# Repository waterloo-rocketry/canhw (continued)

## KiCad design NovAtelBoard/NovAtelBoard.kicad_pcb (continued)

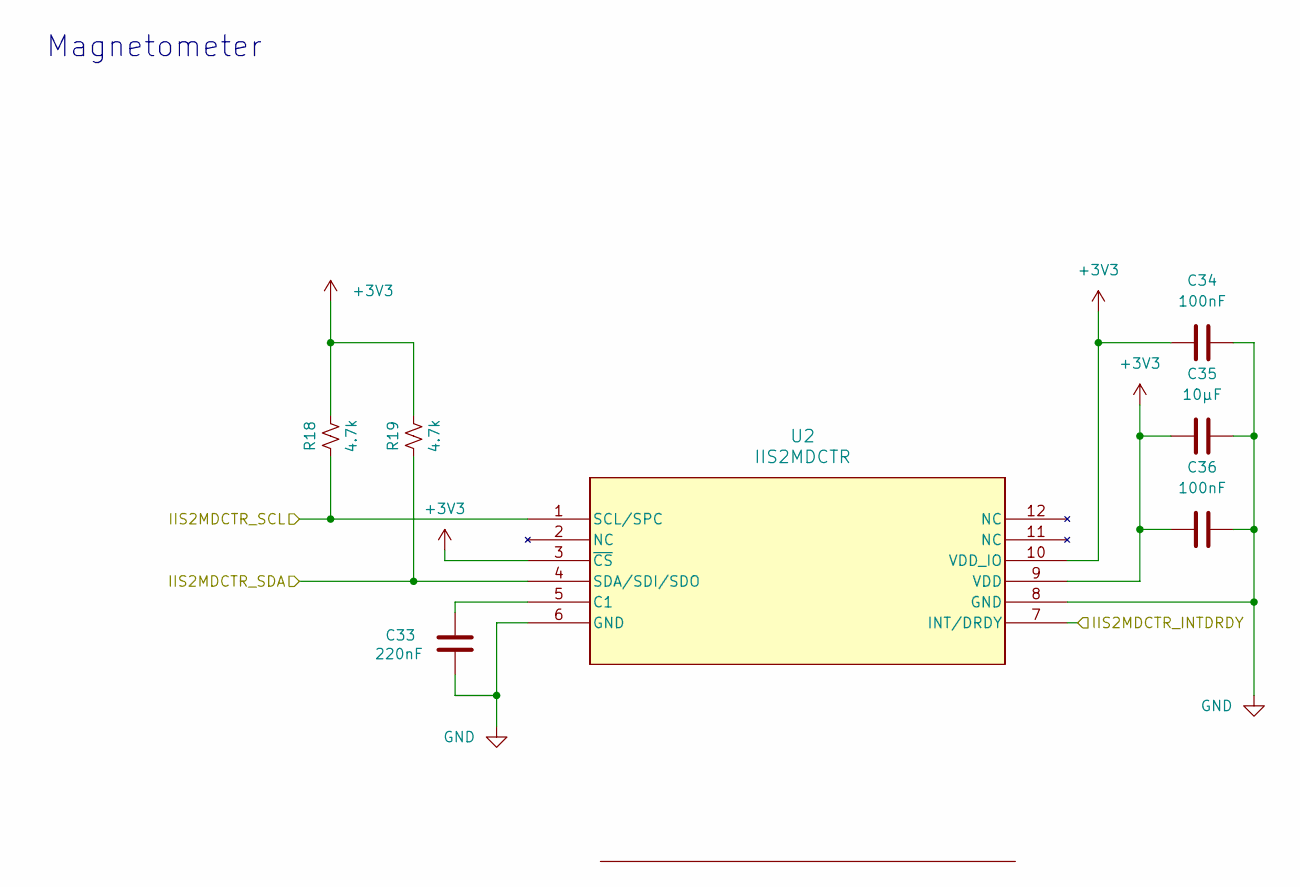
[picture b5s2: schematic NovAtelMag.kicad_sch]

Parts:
C33: 220nF; C_0603_1608Metric_Pad1.08x0.95mm_HandSolder
C34, C36: 100nF; C_0603_1608Metric_Pad1.08x0.95mm_HandSolder
C35: 10μF; C_0603_1608Metric_Pad1.08x0.95mm_HandSolder
R18, R19: 4.7k; R_0402_1005Metric; LCSC Part # C144773
U2: IIS2MDCTR; LGA-12_2X2X0P7_STM

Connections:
+3V3: C34.1, C35.2, C36.2, R18.1, R19.1, U2.3 (~CS), U2.9 (VDD), U2.10 (VDD_IO); also elsewhere on the board
/NovAtelMag/IIS2MDCTR_INTDRDY: U2.7 (INT/DRDY); also elsewhere on the board
/NovAtelMag/IIS2MDCTR_SCL: R18.2, U2.1 (SCL/SPC); also elsewhere on the board
/NovAtelMag/IIS2MDCTR_SDA: R19.2, U2.4 (SDA/SDI/SDO); also elsewhere on the board
GND: C33.1, C34.2, C35.1, C36.1, U2.6 (GND), U2.8 (GND); also elsewhere on the board
unnamed: C33.2, U2.5 (C1)

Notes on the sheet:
Magnetometer

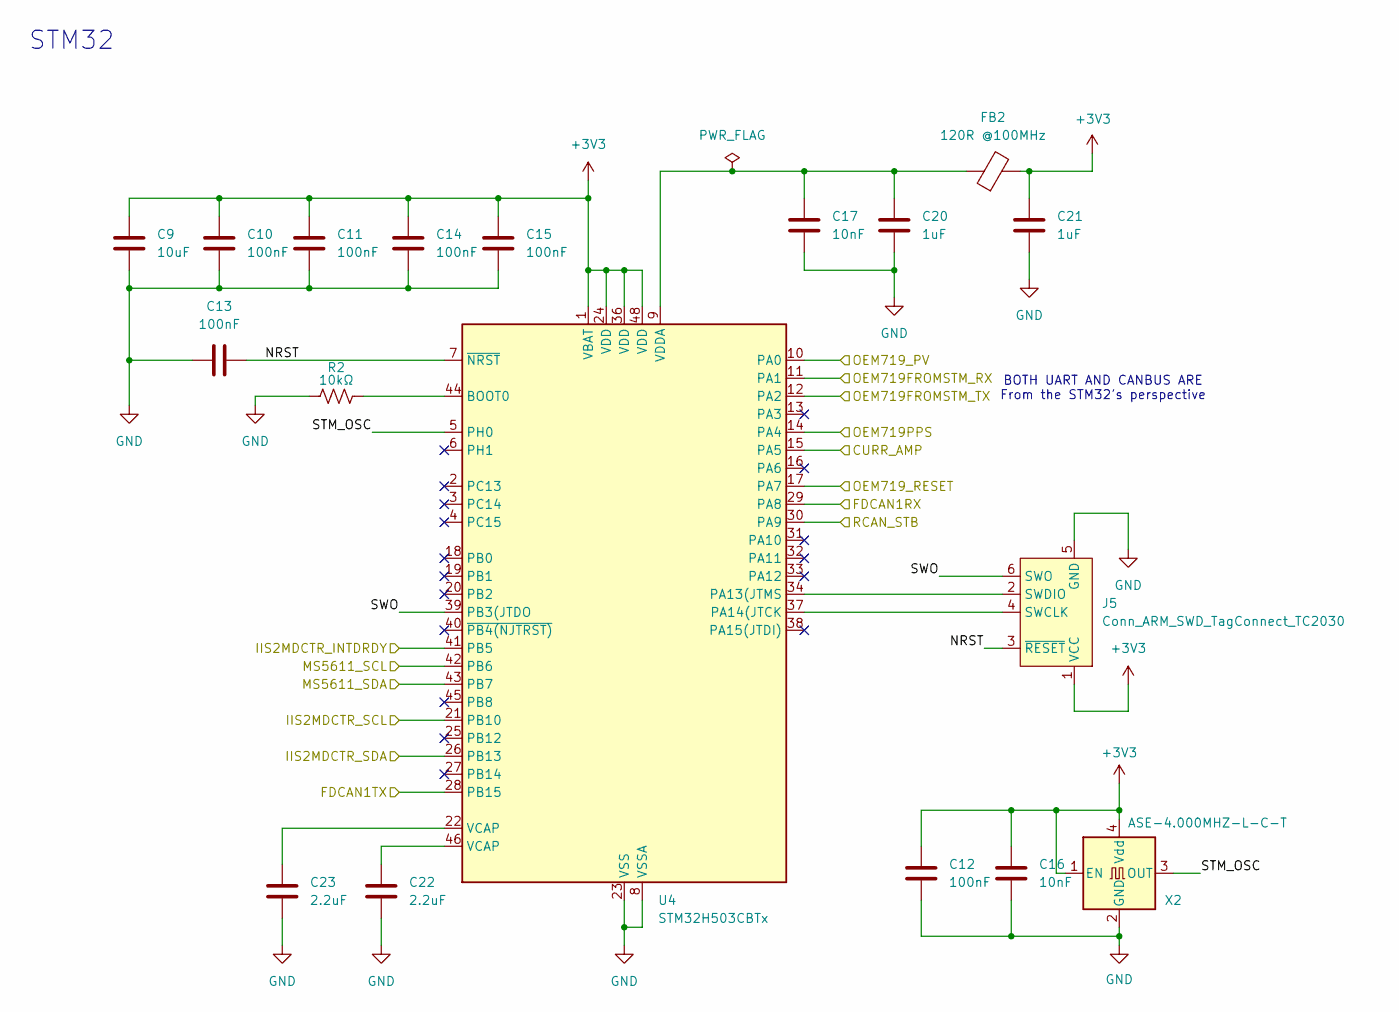
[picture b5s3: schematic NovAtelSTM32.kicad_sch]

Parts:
C9: 10uF; C_0603_1608Metric_Pad1.08x0.95mm_HandSolder
C10, C11, C12, C13, C14, C15: 100nF; C_0603_1608Metric_Pad1.08x0.95mm_HandSolder
C16, C17: 10nF; C_0603_1608Metric_Pad1.08x0.95mm_HandSolder
C20, C21: 1uF; C_0603_1608Metric_Pad1.08x0.95mm_HandSolder
C22, C23: 2.2uF; C_0603_1608Metric_Pad1.08x0.95mm_HandSolder
FB2: 120R @100MHz
J5: Conn_ARM_SWD_TagConnect_TC2030; Tag-Connect_TC2030-IDC-FP_2x03_P1.27mm_Vertical
R2: 10kΩ; R_Array_SIP4
U4: STM32H503CBTx; LQFP-48_7x7mm_P0.5mm
X2: ASE-4.000MHZ-L-C-T; Oscillator_SMD_Abracon_ASE-4Pin_3.2x2.5mm; LCSC Part # C437121

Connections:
+3V3: C9.1, C10.1, C11.1, C12.1, C14.1, C15.1, C16.1, C21.1, FB2.2, J5.1 (VCC), U4.1 (VBAT), U4.24 (VDD), U4.36 (VDD), U4.48 (VDD), X2.1 (EN), X2.4 (Vdd); also elsewhere on the board
/NovAtelBaro/MS5611_SCL: U4.42 (PB6); also elsewhere on the board
/NovAtelBaro/MS5611_SDA: U4.43 (PB7); also elsewhere on the board
/NovAtelConnAndCan/CURR_AMP: U4.15 (PA5); also elsewhere on the board
/NovAtelConnAndCan/FDCAN1RX: U4.29 (PA8); also elsewhere on the board
/NovAtelConnAndCan/FDCAN1TX: U4.28 (PB15); also elsewhere on the board
/NovAtelConnAndCan/RCAN_STB: U4.30 (PA9); also elsewhere on the board
/NovAtelHeader/OEM719PPS: U4.14 (PA4); also elsewhere on the board
/NovAtelHeader/OEM719_PV: U4.10 (PA0); also elsewhere on the board
/NovAtelHeader/OEM719_RX: U4.12 (PA2); also elsewhere on the board
/NovAtelHeader/OEM719_TX: U4.11 (PA1); also elsewhere on the board
/NovAtelHeader/~OEM719_RESET: U4.17 (PA7); also elsewhere on the board
/NovAtelMag/IIS2MDCTR_INTDRDY: U4.41 (PB5); also elsewhere on the board
/NovAtelMag/IIS2MDCTR_SCL: U4.21 (PB10); also elsewhere on the board
/NovAtelMag/IIS2MDCTR_SDA: U4.26 (PB13); also elsewhere on the board
/NovAtelSTM32/NRST: C13.1, J5.3 (~RESET), U4.7 (~NRST)
/NovAtelSTM32/STM_OSC: U4.5 (PH0), X2.3 (OUT)
/NovAtelSTM32/SWO: J5.6 (SWO), U4.39 (PB3(JTDO)
GND: C9.2, C10.2, C11.2, C12.2, C13.2, C14.2, C15.2, C16.2, C17.2, C20.2, C21.2, C22.2, C23.2, J5.5 (GND), R2.1, U4.8 (VSSA), U4.23 (VSS), U4.35 (VSS), U4.47 (VSS), X2.2 (GND); also elsewhere on the board
unnamed: C22.1, U4.46 (VCAP)
unnamed: C23.1, U4.22 (VCAP)
unnamed: J5.4 (SWCLK), U4.37 (PA14(JTCK)
unnamed: J5.2 (SWDIO), U4.34 (PA13(JTMS)
unnamed: R2.2, U4.44 (BOOT0)
unnamed: C17.1, C20.1, FB2.1, U4.9 (VDDA)

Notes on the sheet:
STM32
BOTH UART AND CANBUS ARE From the STM32's perspective

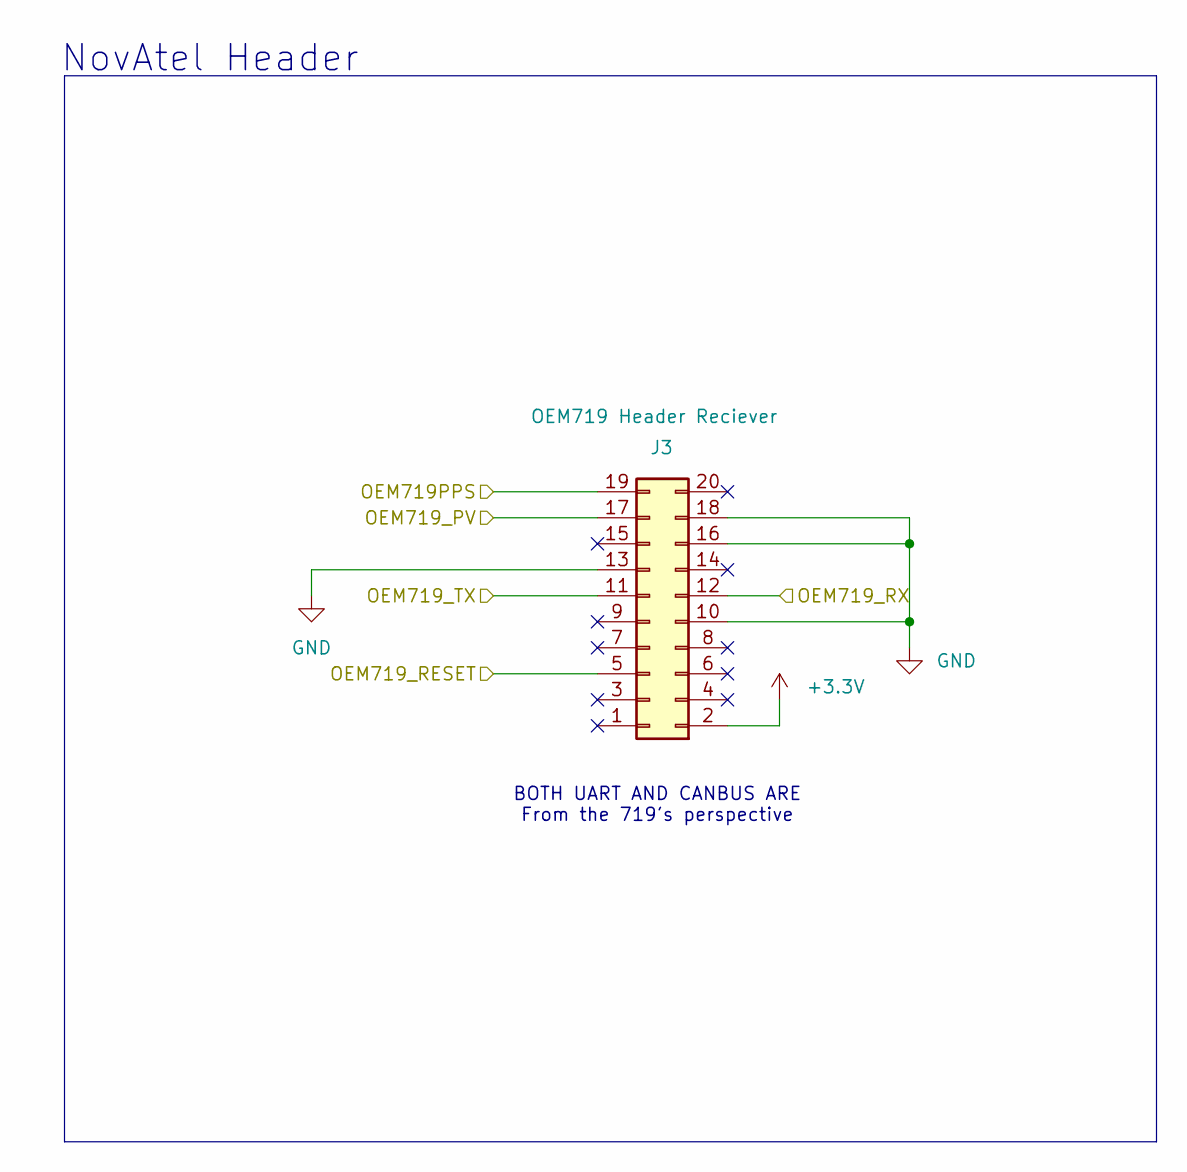
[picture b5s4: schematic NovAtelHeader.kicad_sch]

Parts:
J3: OEM719 Header Reciever

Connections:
unnamed: J3.10 (GND), J3.13 (GND), J3.16 (GND), J3.18 (GND)

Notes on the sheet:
NovAtel Header
BOTH UART AND CANBUS ARE From the 719's perspective

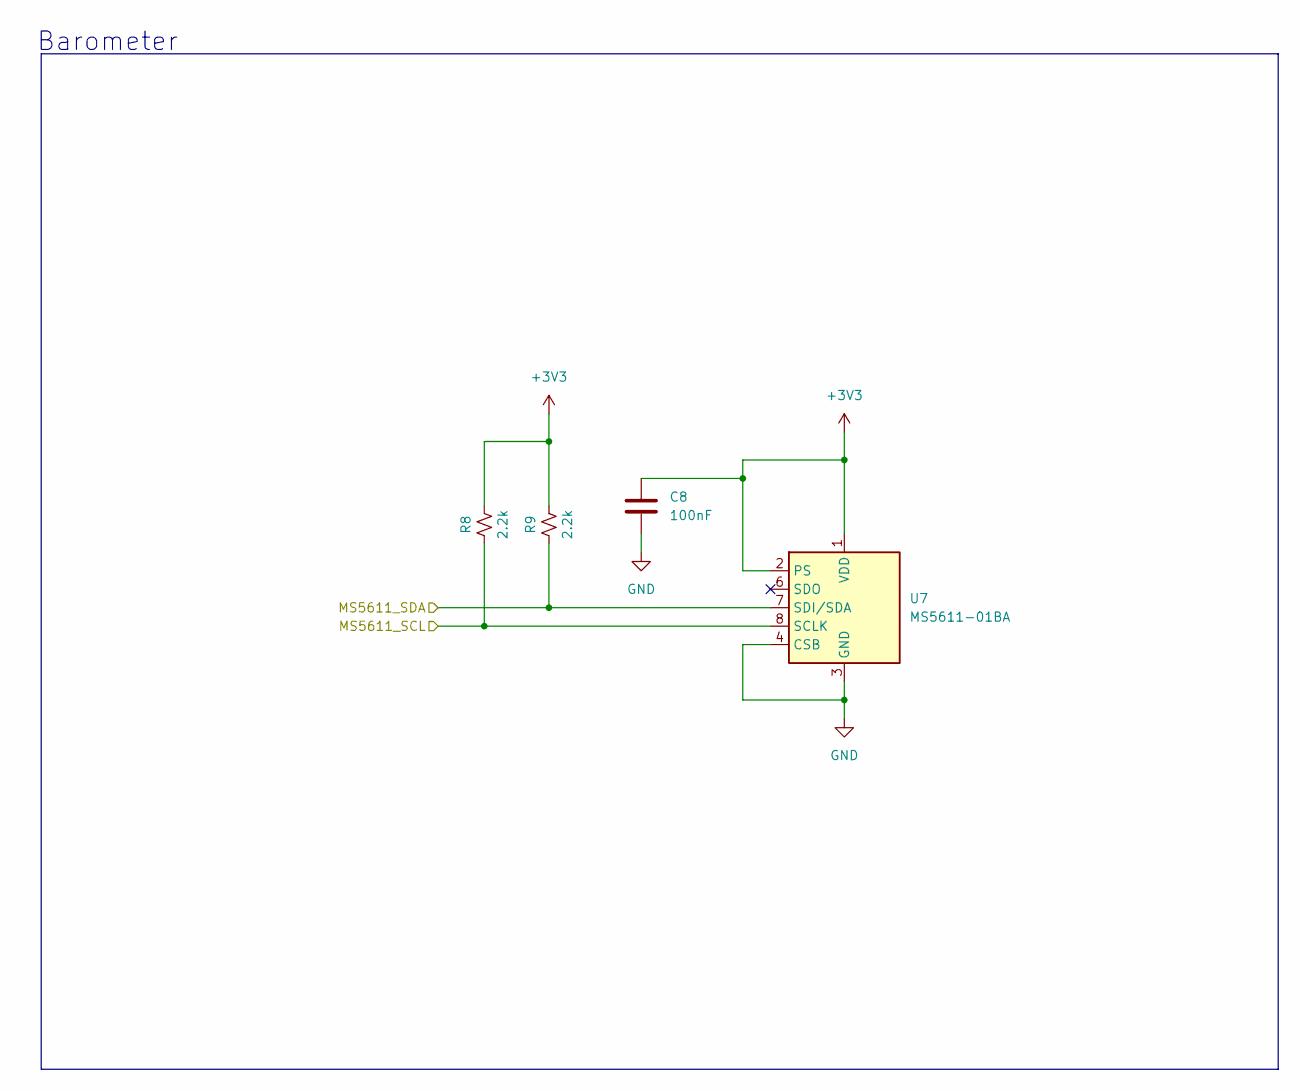
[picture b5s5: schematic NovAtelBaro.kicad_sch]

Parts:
C8: 100nF; C_0603_1608Metric_Pad1.08x0.95mm_HandSolder
R8, R9: 2.2k; R_0402_1005Metric; LCSC Part # C144773
U7: MS5611-01BA; LGA-8_3x5mm_P1.25mm

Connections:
+3V3: C8.1, R8.1, R9.1, U7.1 (VDD), U7.2 (PS); also elsewhere on the board
/NovAtelBaro/MS5611_SCL: R8.2, U7.8 (SCLK); also elsewhere on the board
/NovAtelBaro/MS5611_SDA: R9.2, U7.7 (SDI/SDA); also elsewhere on the board
GND: C8.2, U7.3 (GND), U7.4 (CSB), U7.5 (CSB); also elsewhere on the board

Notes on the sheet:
Barometer

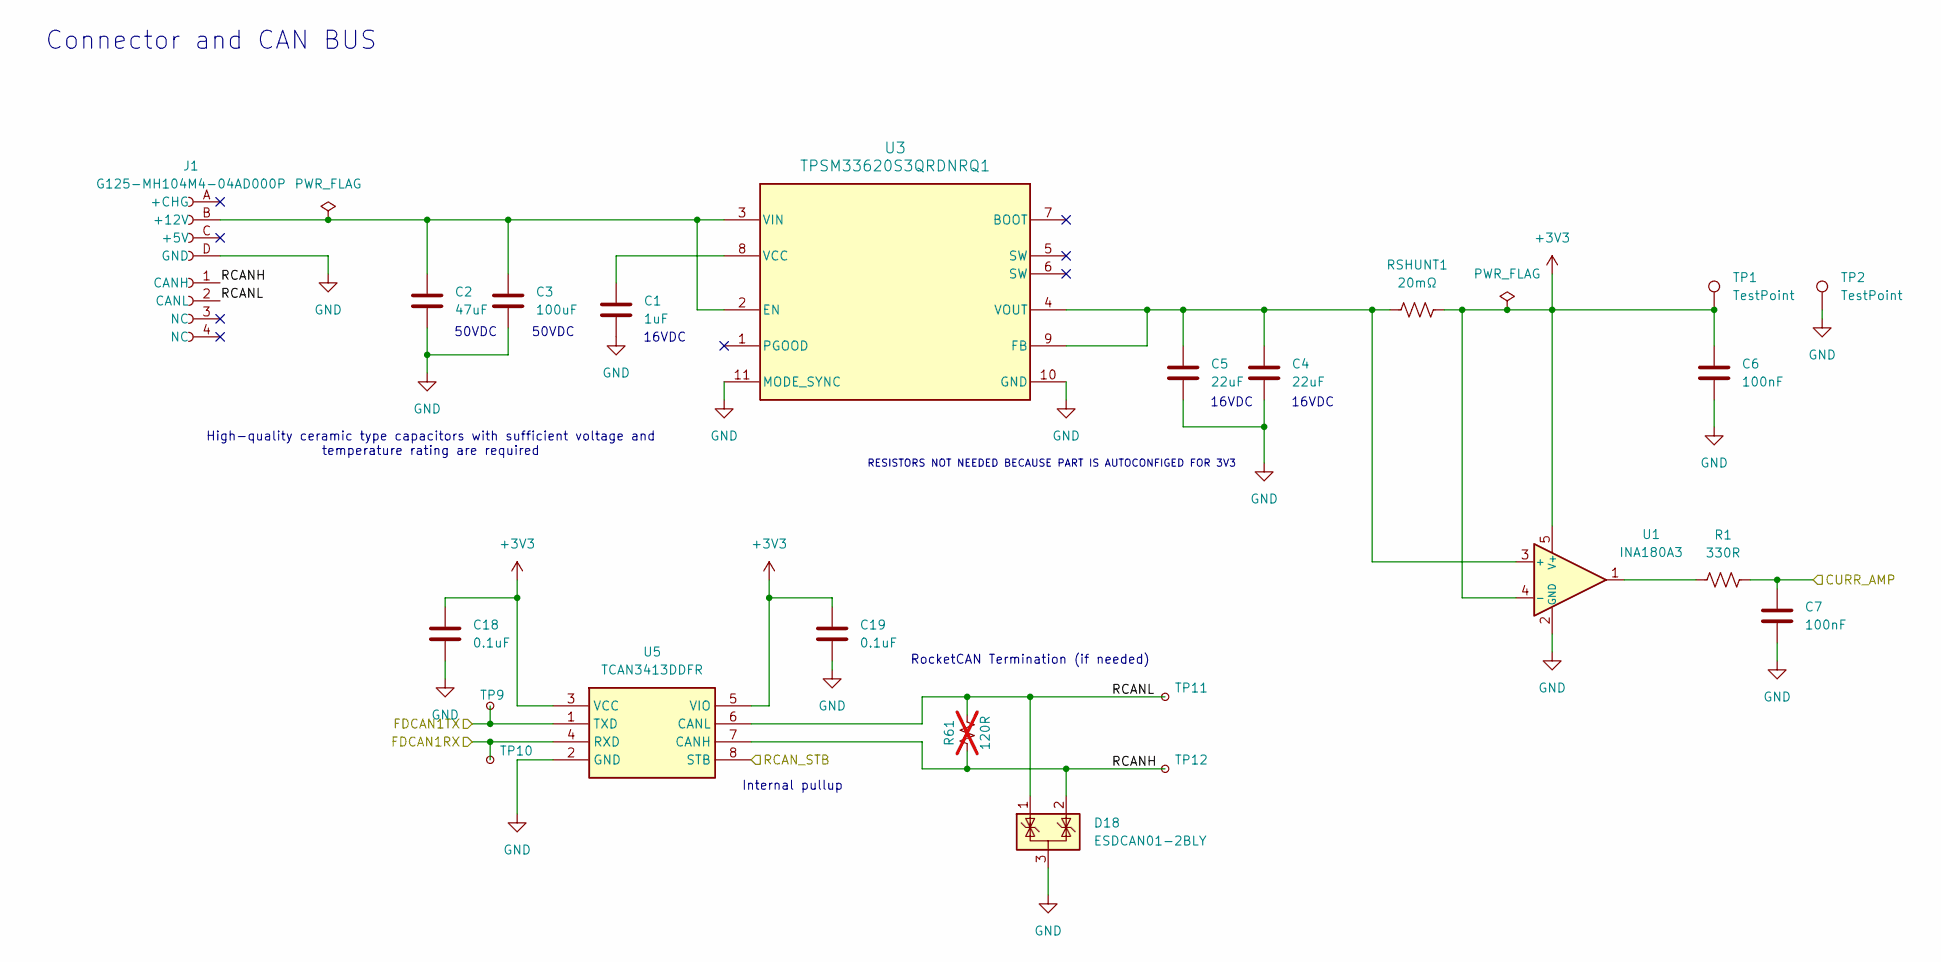
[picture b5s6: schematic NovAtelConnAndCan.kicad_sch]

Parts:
C1: 1uF; C_0603_1608Metric_Pad1.08x0.95mm_HandSolder
C2: 47uF; C_0603_1608Metric_Pad1.08x0.95mm_HandSolder
C3: 100uF; C_0603_1608Metric_Pad1.08x0.95mm_HandSolder
C4, C5: 22uF; C_0603_1608Metric_Pad1.08x0.95mm_HandSolder
C6, C7: 100nF; C_0603_1608Metric_Pad1.08x0.95mm_HandSolder
C18, C19: 0.1uF; C_0603_1608Metric_Pad1.08x0.95mm_HandSolder
D18: ESDCAN01-2BLY; SOT-23; LCSC Part # C1976606
J1: G125-MH104M4-04AD000P; connector_Harwin_G125–MG10605M4P
R1: 330R; DIP-8_W7.62mm
R61: 120R; R_0805_2012Metric; not fitted
RSHUNT1: 20mΩ; DIP-8_W7.62mm
TP1, TP2: TestPoint; SOT-23-5
TP9: RCAN_TX; TestPoint_Pad_D1.0mm
TP10: RCAN_RX; TestPoint_Pad_D1.0mm
TP11: RCAN_L; TestPoint_Pad_D1.0mm
TP12: RCAN_H; TestPoint_Pad_D1.0mm
U1: INA180A3; SOT-23-5
U3: TPSM33620S3QRDNRQ1; RDN0011B-MFG
U5: TCAN3413DDFR; Mouser Part Number 595-TCAN3413DDFR

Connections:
+3V3: C6.1, C18.1, C19.1, RSHUNT1.2, TP1.1 (1_1), U1.4 (-), U1.5 (V+), U5.3 (VCC), U5.5 (VIO); also elsewhere on the board
/NovAtelConnAndCan/CURR_AMP: C7.1, R1.2; also elsewhere on the board
/NovAtelConnAndCan/FDCAN1RX: TP10.1 (1_1), U5.4 (RXD); also elsewhere on the board
/NovAtelConnAndCan/FDCAN1TX: TP9.1 (1_1), U5.1 (TXD); also elsewhere on the board
/NovAtelConnAndCan/RCANH: D18.2 (K), J1.1 (CANH), R61.2, TP12.1 (1_1), U5.7 (CANH)
/NovAtelConnAndCan/RCANL: D18.1 (K), J1.2 (CANL), R61.1, TP11.1 (1_1), U5.6 (CANL)
/NovAtelConnAndCan/RCAN_STB: U5.8 (STB); also elsewhere on the board
GND: C1.2, C2.2, C3.2, C4.1, C5.2, C6.2, C7.2, C18.2, C19.2, D18.3 (A), J1.D (GND), TP2.1 (1_1), U1.2 (GND), U3.10 (GND), U3.11 (MODE_SYNC), U5.2 (GND); also elsewhere on the board
unnamed: C2.1, C3.1, J1.B (+12V), U3.2 (EN), U3.3 (VIN)
unnamed: R1.1, U1.1
unnamed: C4.2, C5.1, RSHUNT1.1, U1.3 (+), U3.4 (VOUT), U3.9 (FB)
unnamed: C1.1, U3.8 (VCC)

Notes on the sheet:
50VDC
16VDC
16VDC
High-quality ceramic type capacitors with sufficient voltage and temperature rating are required
Connector and CAN BUS
RocketCAN Termination (if needed)
Internal pullup
RESISTORS NOT NEEDED BECAUSE PART IS AUTOCONFIGED FOR 3V3

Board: 2 copper layers, 52 parts (0 on the bottom side), 32 nets, no tracks yet.

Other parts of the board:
J2: OEM719 Header Reciever; PinSocket_2x10_P2.54mm_Vertical

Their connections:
+3V3: J2.2 (3V3); also elsewhere on the board
/NovAtelHeader/OEM719PPS: J2.19 (PPS); also elsewhere on the board
/NovAtelHeader/OEM719_PV: J2.17 (PV); also elsewhere on the board
/NovAtelHeader/OEM719_RX: J2.12 (RXD1); also elsewhere on the board
/NovAtelHeader/OEM719_TX: J2.11 (TXD1); also elsewhere on the board
/NovAtelHeader/~OEM719_RESET: J2.5 (nRESET_IN); also elsewhere on the board
GND: J2.10 (GND), J2.13 (GND), J2.16 (GND), J2.18 (GND); also elsewhere on the board

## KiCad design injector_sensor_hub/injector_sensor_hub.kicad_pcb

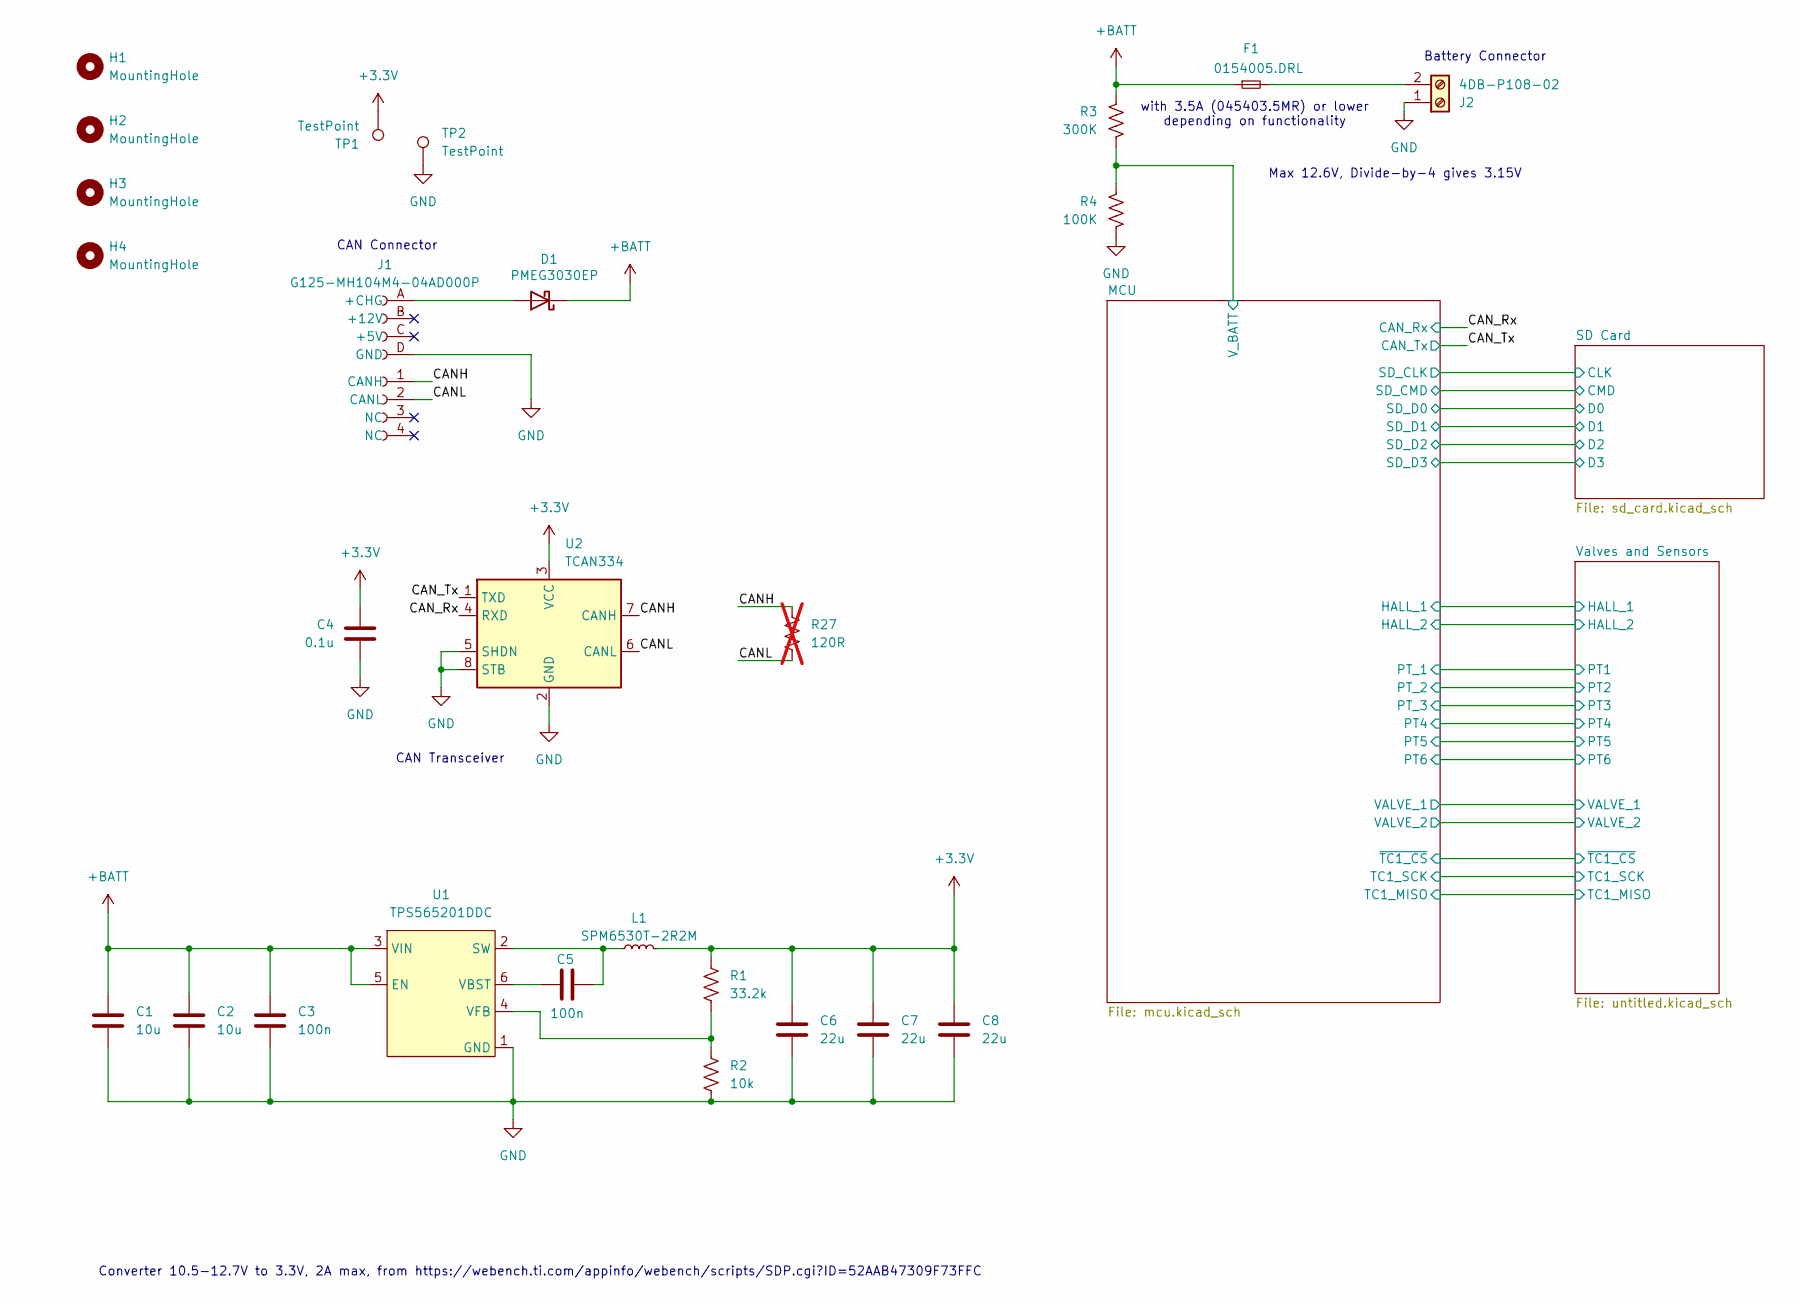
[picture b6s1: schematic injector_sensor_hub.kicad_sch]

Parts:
C1, C2: 10u; C_0603_1608Metric_Pad1.08x0.95mm_HandSolder
C3, C5: 100n; C_0603_1608Metric_Pad1.08x0.95mm_HandSolder
C4: 0.1u; C_0603_1608Metric_Pad1.08x0.95mm_HandSolder
C6, C7, C8: 22u; C_0603_1608Metric_Pad1.08x0.95mm_HandSolder
D1: PMEG3030EP; D_SOD-128
F1: 0154005.DRL; FUSE_0154005.DR
H1, H2, H3, H4: MountingHole; MountingHole_3.2mm_M3_ISO14580
J1: G125-MH104M4-04AD000P; connector_Harwin_G125-MH104M4-04AD000P
J2: 4DB-P108-02
L1: SPM6530T-2R2M; IND_SPM6530T-2R2M
R1: 33.2k; R_0603_1608Metric_Pad0.98x0.95mm_HandSolder
R2: 10k; R_0603_1608Metric_Pad0.98x0.95mm_HandSolder
R3: 300K; R_0603_1608Metric_Pad0.98x0.95mm_HandSolder
R4: 100K; R_0603_1608Metric_Pad0.98x0.95mm_HandSolder
R27: 120R; R_0603_1608Metric_Pad0.98x0.95mm_HandSolder; not fitted
TP1: TestPoint; TestPoint_Pad_D2.0mm
TP2: TestPoint; TestPoint_Keystone_5000-5004_Miniature
U1: TPS565201DDC; SOT-23-6_Handsoldering
U2: TCAN334; SOIC-8_3.9x4.9mm_P1.27mm

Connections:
+3.3V: C4.1, C6.1, C7.1, C8.1, L1.1, R1.1, TP1.1, U2.3 (VCC); also elsewhere on the board
+BATT: C1.1, C2.1, C3.1, D1.1 (K), F1.1, R3.1, U1.3 (VIN), U1.5 (EN); also elsewhere on the board
/CANH: J1.1 (CANH), R27.1, U2.7 (CANH)
/CANL: J1.2 (CANL), R27.2, U2.6 (CANL)
/CAN_Rx: U2.4 (RXD); also elsewhere on the board
/CAN_Tx: U2.1 (TXD); also elsewhere on the board
/MCU/V_BATT: R3.2, R4.1; also elsewhere on the board
GND: C1.2, C2.2, C3.2, C4.2, C6.2, C7.2, C8.2, J1.D (GND), J2.1, R2.2, R4.2, TP2.1, U1.1 (GND), U2.2 (GND), U2.5 (SHDN), U2.8 (STB); also elsewhere on the board
unnamed: D1.2 (A), J1.A (+CHG)
unnamed: F1.2, J2.2
unnamed: C5.1, L1.2, U1.2 (SW)
unnamed: C5.2, U1.6 (VBST)
unnamed: R1.2, R2.1, U1.4 (VFB)

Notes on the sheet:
Converter 10.5-12.7V to 3.3V, 2A max, from https://webench.ti.com/appinfo/webench/scripts/SDP.cgi?ID=52AAB47309F73FFC
Max 12.6V, Divide-by-4 gives 3.15V
with 3.5A (045403.5MR) or lower depending on functionality
CAN Connector
Battery Connector
CAN Transceiver

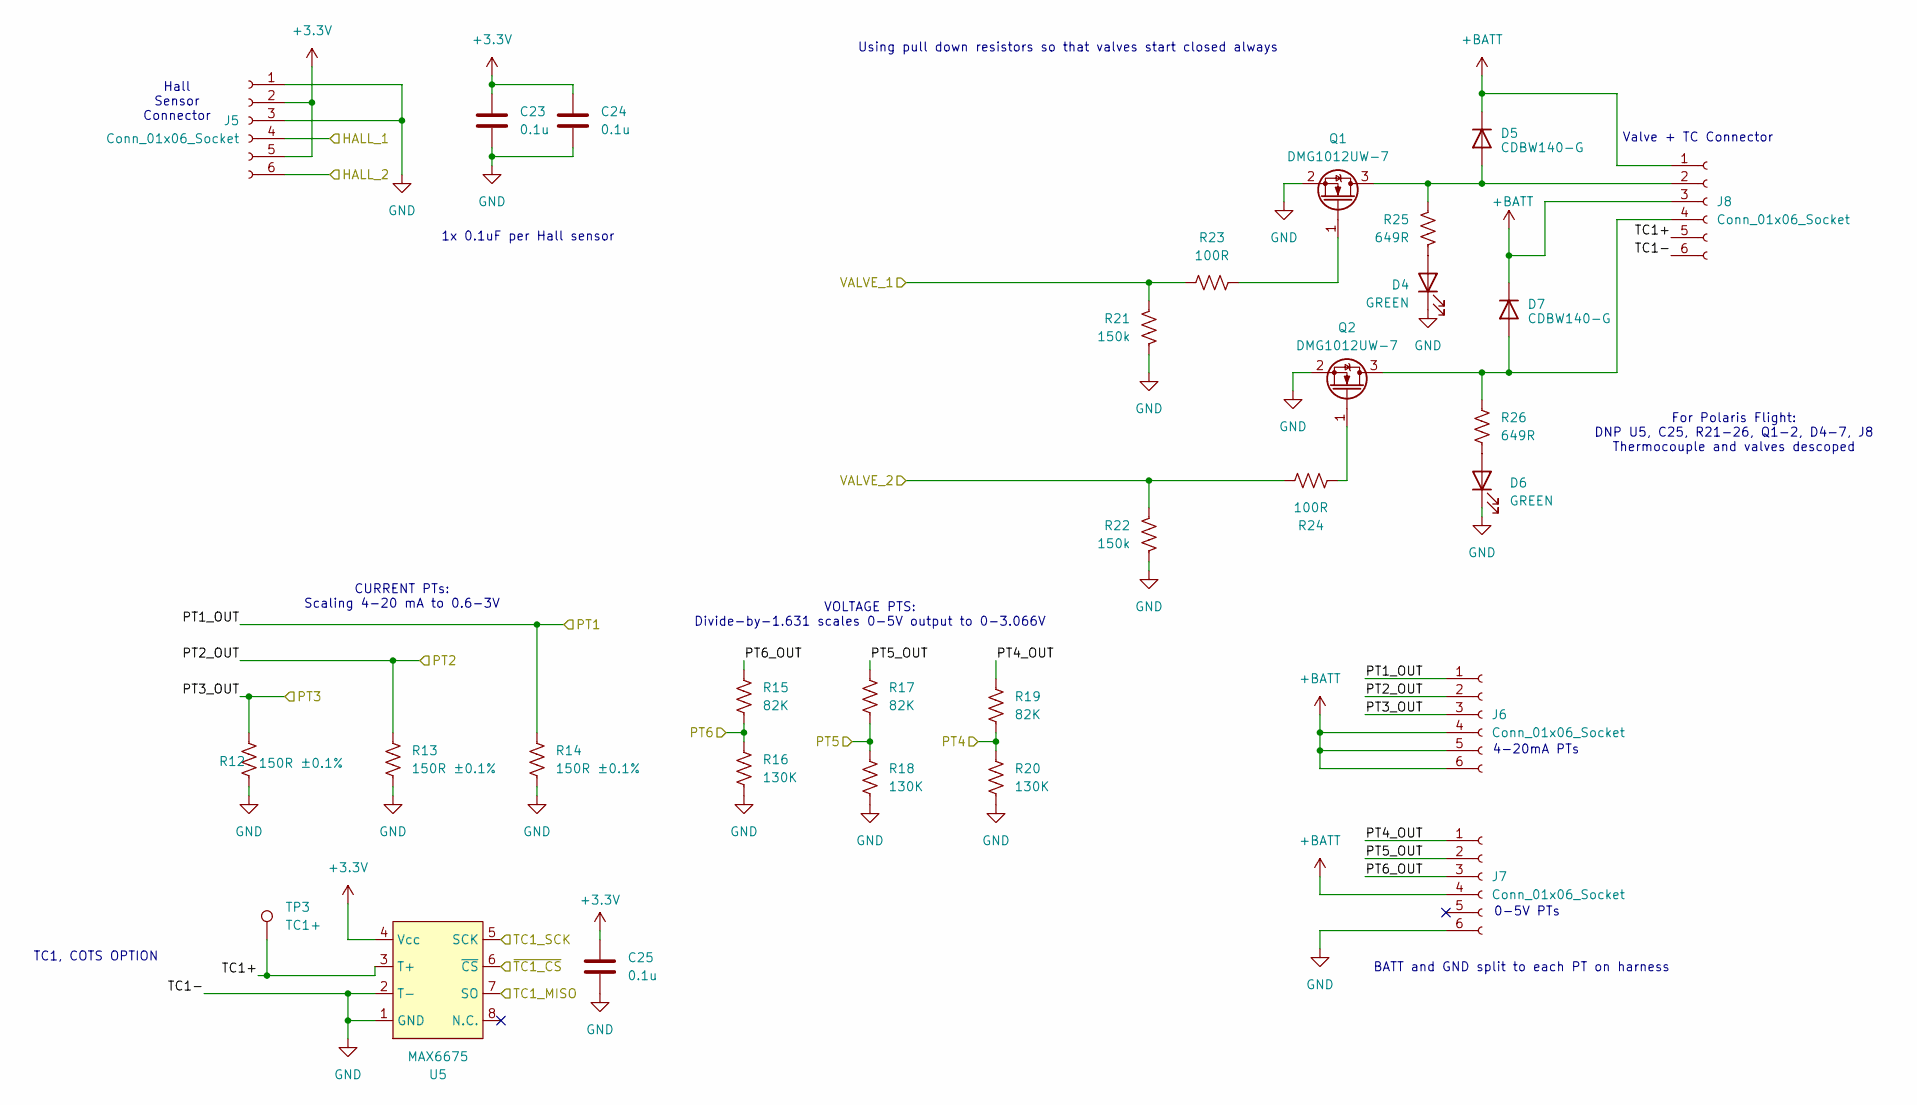
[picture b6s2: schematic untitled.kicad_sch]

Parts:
C23, C24, C25: 0.1u; C_0603_1608Metric_Pad1.08x0.95mm_HandSolder
D4, D6: GREEN; LED_1206_3216Metric_Pad1.42x1.75mm_HandSolder
D5, D7: CDBW140-G; D_SOD-123
J5, J6, J7, J8: Conn_01x06_Socket; connector_Harwin_G125–MG10605M4P
Q1, Q2: DMG1012UW-7; SOT_12UW-7_DIO
R12, R13, R14: 150R ±0.1%; R_0603_1608Metric_Pad0.98x0.95mm_HandSolder
R15, R17, R19: 82K; R_0603_1608Metric_Pad0.98x0.95mm_HandSolder
R16, R18, R20: 130K; R_0603_1608Metric_Pad0.98x0.95mm_HandSolder
R21, R22: 150k; R_0603_1608Metric_Pad0.98x0.95mm_HandSolder
R23, R24: 100R; R_0603_1608Metric_Pad0.98x0.95mm_HandSolder
R25, R26: 649R; R_0603_1608Metric_Pad0.98x0.95mm_HandSolder
TP3: TC1+; TestPoint_Pad_D2.0mm
U5: MAX6675; SOIC-8_3.9x4.9mm_P1.27mm

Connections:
+3.3V: C23.1, C24.1, C25.1, J5.2, J5.5, U5.4 (Vcc); also elsewhere on the board
+BATT: D5.1 (K), D7.1 (K), J6.4, J6.5, J6.6, J7.4, J8.1, J8.3; also elsewhere on the board
/MCU/HALL_1: J5.4; also elsewhere on the board
/MCU/HALL_2: J5.6; also elsewhere on the board
/MCU/PT4: R19.2, R20.1; also elsewhere on the board
/MCU/PT5: R17.2, R18.1; also elsewhere on the board
/MCU/PT6: R15.2, R16.1; also elsewhere on the board
/MCU/TC1_MISO: U5.7 (SO); also elsewhere on the board
/MCU/TC1_SCK: U5.5 (SCK); also elsewhere on the board
/MCU/VALVE_1: R21.2, R23.2; also elsewhere on the board
/MCU/VALVE_2: R22.1, R24.2; also elsewhere on the board
/MCU/~TC1_CS: U5.6 (~CS); also elsewhere on the board
/Valves and Sensors/PT1_OUT: J6.1, R14.1; also elsewhere on the board
/Valves and Sensors/PT2_OUT: J6.2, R13.1; also elsewhere on the board
/Valves and Sensors/PT3_OUT: J6.3, R12.1; also elsewhere on the board
/Valves and Sensors/PT4_OUT: J7.1, R19.1
/Valves and Sensors/PT5_OUT: J7.2, R17.1
/Valves and Sensors/PT6_OUT: J7.3, R15.1
/Valves and Sensors/TC1+: J8.5, TP3.1, U5.3 (T+); also elsewhere on the board
GND: C23.2, C24.2, C25.2, D4.1 (K), D6.1 (K), J5.1, J5.3, J7.6, J8.6, Q1.2 (S), Q2.2 (S), R12.2, R13.2, R14.2, R16.2, R18.2, R20.2, R21.1, R22.2, U5.1 (GND), U5.2 (T-); also elsewhere on the board
unnamed: D4.2 (A), R25.1
unnamed: D5.2 (A), J8.2, Q1.3 (D), R25.2
unnamed: D6.2 (A), R26.2
unnamed: D7.2 (A), J8.4, Q2.3 (D), R26.1
unnamed: Q1.1 (G), R23.1
unnamed: Q2.1 (G), R24.1

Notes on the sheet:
Hall Sensor Connector
0-5V PTs
Valve + TC Connector
1x 0.1uF per Hall sensor
CURRENT PTs: Scaling 4-20 mA to 0.6-3V
For Polaris Flight: DNP U5, C25, R21-26, Q1-2, D4-7, J8 Thermocouple and valves descoped
BATT and GND split to each PT on harness
Using pull down resistors so that valves start closed always
4-20mA PTs
TC1, COTS OPTION
VOLTAGE PTS: Divide-by-1.631 scales 0-5V output to 0-3.066V

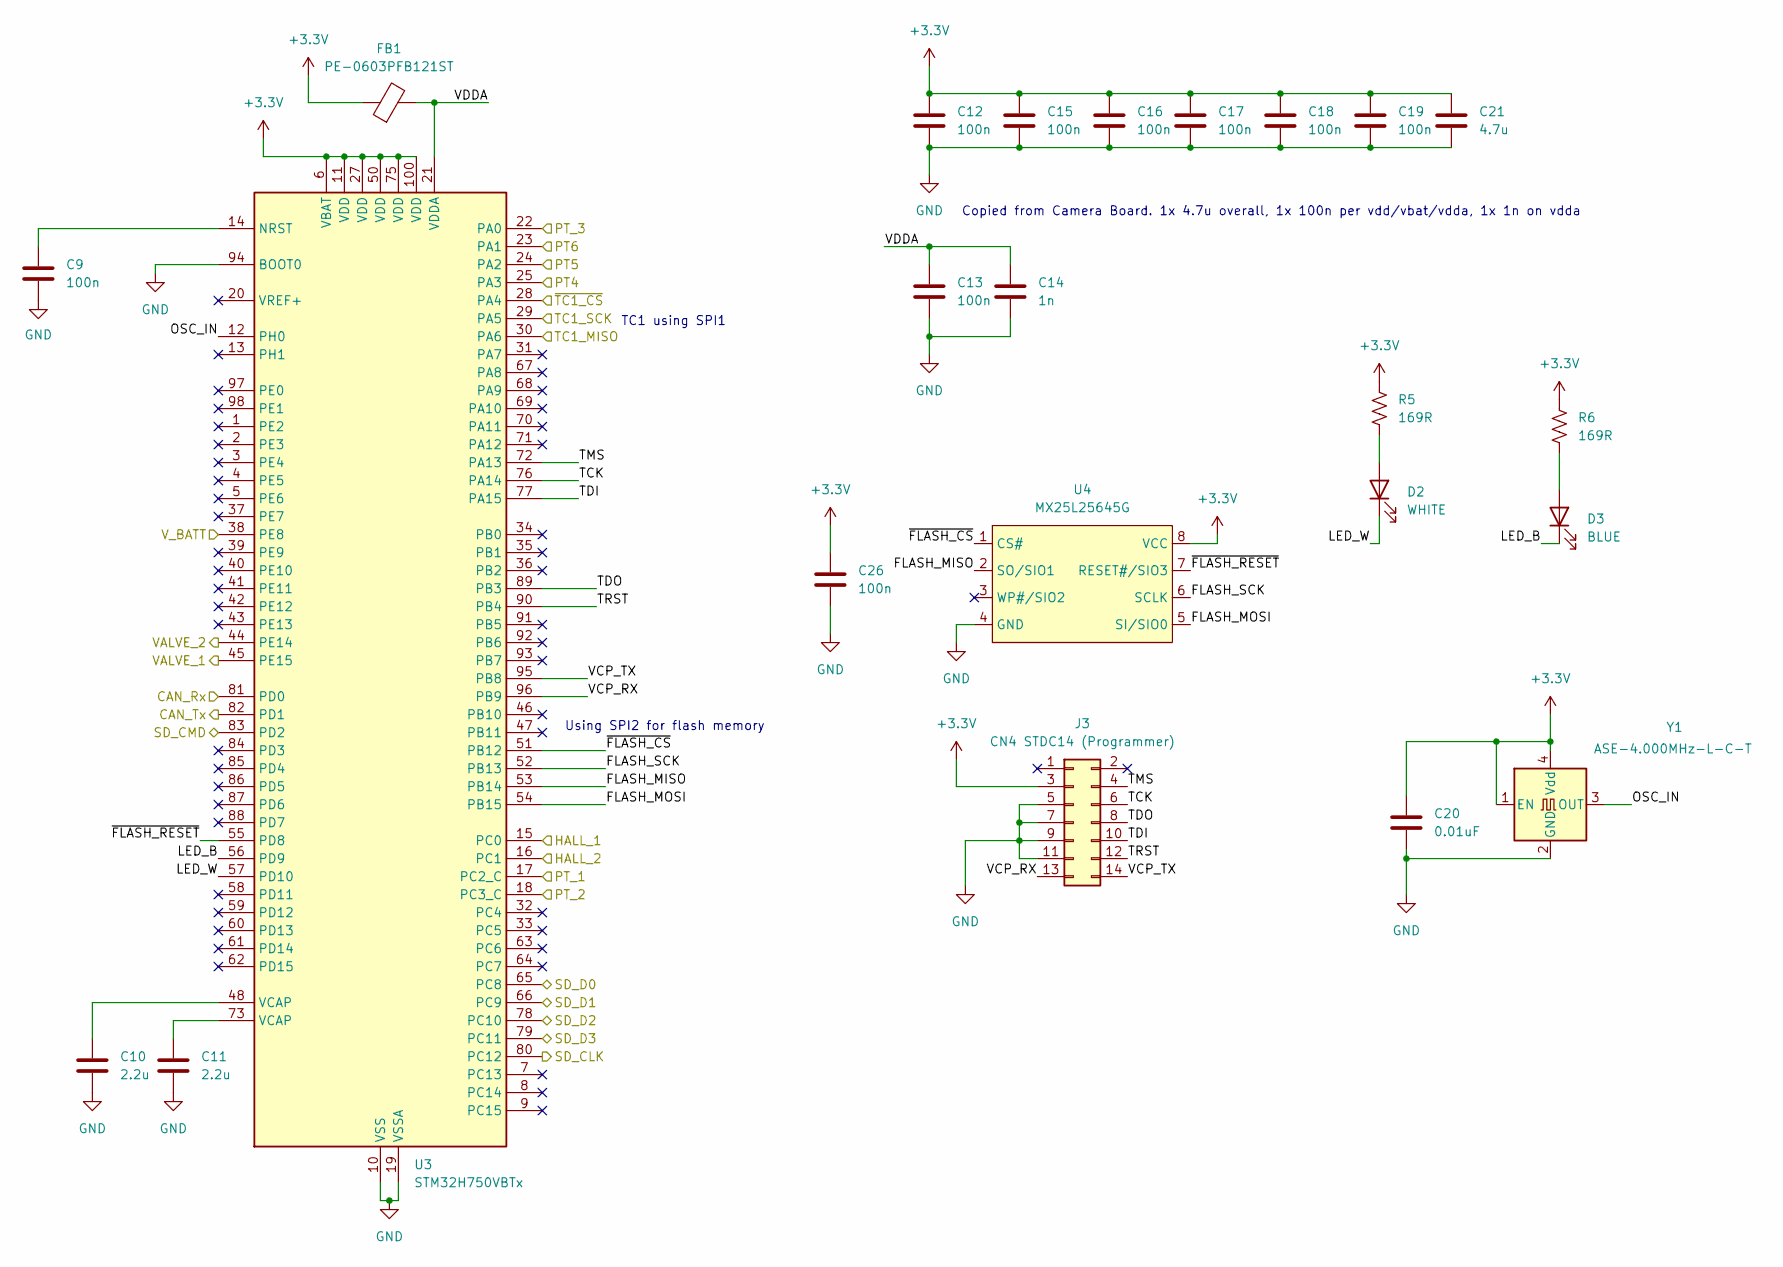
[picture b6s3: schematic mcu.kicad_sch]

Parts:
C9, C12, C13, C15, C16, C17, C18, C19, C26: 100n; C_0603_1608Metric_Pad1.08x0.95mm_HandSolder
C10, C11: 2.2u; C_0603_1608Metric_Pad1.08x0.95mm_HandSolder
C14: 1n; C_0603_1608Metric_Pad1.08x0.95mm_HandSolder
C20: 0.01uF; C_0603_1608Metric_Pad1.08x0.95mm_HandSolder
C21: 4.7u; C_0603_1608Metric_Pad1.08x0.95mm_HandSolder
D2: WHITE; LED_1206_3216Metric_Pad1.42x1.75mm_HandSolder
D3: BLUE; LED_1206_3216Metric_Pad1.42x1.75mm_HandSolder
FB1: PE-0603PFB121ST; R_0603_1608Metric_Pad0.98x0.95mm_HandSolder
J3: CN4 STDC14 (Programmer); PinSocket_2x07_P1.27mm_Vertical_SMD
R5, R6: 169R; R_0603_1608Metric_Pad0.98x0.95mm_HandSolder
U3: STM32H750VBTx; LQFP-100_14x14mm_P0.5mm
U4: MX25L25645G; SOIC-8_5.3x5.3mm_P1.27mm
Y1: ASE-4.000MHz-L-C-T; Oscillator_SMD_Abracon_ASE-4Pin_3.2x2.5mm

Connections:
+3.3V: C12.1, C15.1, C16.1, C17.1, C18.1, C19.1, C20.1, C21.1, C26.1, FB1.1, J3.3, R5.1, R6.1, U3.6 (VBAT), U3.11 (VDD), U3.27 (VDD), U3.50 (VDD), U3.75 (VDD), U3.100 (VDD), U4.8 (VCC), Y1.1 (EN), Y1.4 (Vdd); also elsewhere on the board
/CAN_Rx: U3.81 (PD0); also elsewhere on the board
/CAN_Tx: U3.82 (PD1); also elsewhere on the board
/MCU/FLASH_MISO: U3.53 (PB14), U4.2 (SO/SIO1)
/MCU/FLASH_MOSI: U3.54 (PB15), U4.5 (SI/SIO0)
/MCU/FLASH_SCK: U3.52 (PB13), U4.6 (SCLK)
/MCU/HALL_1: U3.15 (PC0); also elsewhere on the board
/MCU/HALL_2: U3.16 (PC1); also elsewhere on the board
/MCU/LED_B: D3.1 (K), U3.56 (PD9)
/MCU/LED_W: D2.1 (K), U3.57 (PD10)
/MCU/OSC_IN: U3.12 (PH0), Y1.3 (OUT)
/MCU/PT4: U3.25 (PA3); also elsewhere on the board
/MCU/PT5: U3.24 (PA2); also elsewhere on the board
/MCU/PT6: U3.23 (PA1); also elsewhere on the board
/MCU/SD_CLK: U3.80 (PC12); also elsewhere on the board
/MCU/SD_CMD: U3.83 (PD2); also elsewhere on the board
/MCU/SD_D0: U3.65 (PC8); also elsewhere on the board
/MCU/SD_D1: U3.66 (PC9); also elsewhere on the board
/MCU/SD_D2: U3.78 (PC10); also elsewhere on the board
/MCU/SD_D3: U3.79 (PC11); also elsewhere on the board
/MCU/TC1_MISO: U3.30 (PA6); also elsewhere on the board
/MCU/TC1_SCK: U3.29 (PA5); also elsewhere on the board
/MCU/TCK: J3.6, U3.76 (PA14)
/MCU/TDI: J3.10, U3.77 (PA15)
/MCU/TDO: J3.8, U3.89 (PB3)
/MCU/TMS: J3.4, U3.72 (PA13)
/MCU/TRST: J3.12, U3.90 (PB4)
/MCU/VALVE_1: U3.45 (PE15); also elsewhere on the board
/MCU/VALVE_2: U3.44 (PE14); also elsewhere on the board
/MCU/VCP_RX: J3.13, U3.96 (PB9)
/MCU/VCP_TX: J3.14, U3.95 (PB8)
/MCU/VDDA: C13.1, C14.1, FB1.2, U3.21 (VDDA)
/MCU/V_BATT: U3.38 (PE8); also elsewhere on the board
/MCU/~FLASH_CS: U3.51 (PB12), U4.1 (CS#)
/MCU/~FLASH_RESET: U3.55 (PD8), U4.7 (RESET#/SIO3)
/MCU/~TC1_CS: U3.28 (PA4); also elsewhere on the board
/Valves and Sensors/PT1_OUT: U3.17 (PC2_C); also elsewhere on the board
/Valves and Sensors/PT2_OUT: U3.18 (PC3_C); also elsewhere on the board
/Valves and Sensors/PT3_OUT: U3.22 (PA0); also elsewhere on the board
GND: C9.2, C10.2, C11.2, C12.2, C13.2, C14.2, C15.2, C16.2, C17.2, C18.2, C19.2, C20.2, C21.2, C26.2, J3.5, J3.7, J3.9, J3.11, U3.10 (VSS), U3.19 (VSSA), U3.26 (VSS), U3.49 (VSS), U3.74 (VSS), U3.94 (BOOT0), U3.99 (VSS), U4.4 (GND), Y1.2 (GND); also elsewhere on the board
unnamed: C10.1, U3.48 (VCAP)
unnamed: C11.1, U3.73 (VCAP)
unnamed: D2.2 (A), R5.2
unnamed: D3.2 (A), R6.2
unnamed: C9.1, U3.14 (NRST)

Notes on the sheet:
Using SPI2 for flash memory
TC1 using SPI1
Copied from Camera Board. 1x 4.7u overall, 1x 100n per vdd/vbat/vdda, 1x 1n on vdda
